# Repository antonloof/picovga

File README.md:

# picovga
VGA output for a Raspberry pi PICO

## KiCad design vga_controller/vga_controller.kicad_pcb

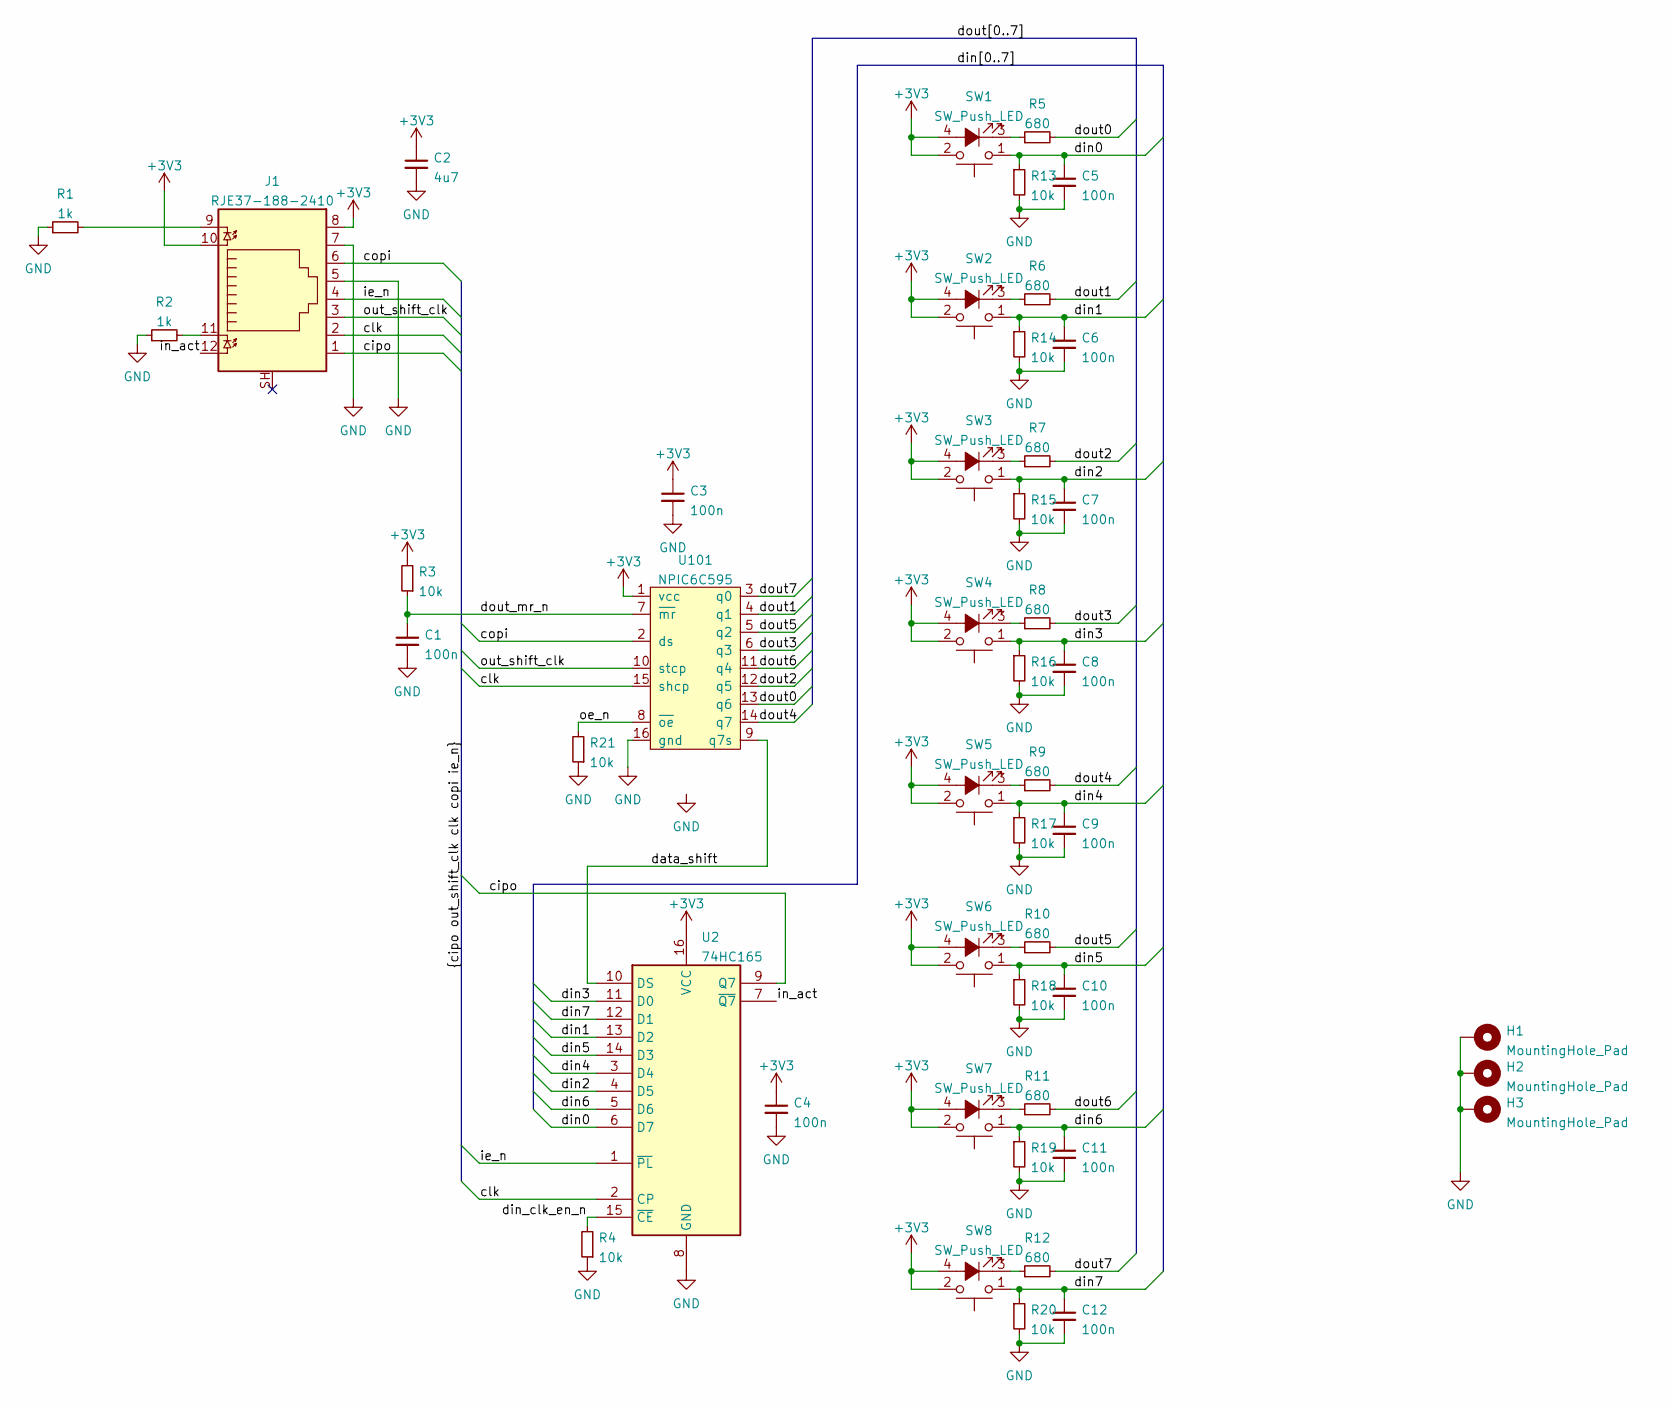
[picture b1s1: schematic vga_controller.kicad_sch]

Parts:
C1, C3, C4, C5, C6, C7, C8, C9, C10, C11, C12: 100n; C_0603_1608Metric_Pad1.08x0.95mm_HandSolder
C2: 4u7; C_0603_1608Metric_Pad1.08x0.95mm_HandSolder
H1, H2, H3: MountingHole_Pad; MountingHole_3.2mm_M3_Pad
J1: RJE37-188-2410; RJ45_Amphenol_RJHSE538X
R1, R2: 1k; R_0603_1608Metric_Pad0.98x0.95mm_HandSolder
R3, R4, R13, R14, R15, R16, R17, R18, R19, R20, R21: 10k; R_0603_1608Metric_Pad0.98x0.95mm_HandSolder
R5, R6, R7, R8, R9, R10, R11, R12: 680; R_0603_1608Metric_Pad0.98x0.95mm_HandSolder
SW1, SW2, SW3, SW4, SW5, SW6, SW7, SW8: SW_Push_LED; SW_Cherry_MX_1.00u_PCB_smd_led
U2: 74HC165; SOIC-16_3.9x9.9mm_P1.27mm
U101: NPIC6C595; SOIC-16_3.9x9.9mm_P1.27mm

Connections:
+3V3: C2.1, C3.1, C4.1, J1.8, J1.10, R3.2, SW1.2, SW1.4 (A), SW2.2, SW2.4 (A), SW3.2, SW3.4 (A), SW4.2, SW4.4 (A), SW5.2, SW5.4 (A), SW6.2, SW6.4 (A), SW7.2, SW7.4 (A), SW8.2, SW8.4 (A), U2.16 (VCC), U101.1 (vcc)
/cipo: J1.1, U2.9 (Q7)
/clk: J1.2, U2.2 (CP), U101.15 (shcp)
/copi: J1.6, U101.2 (ds)
/data_shift: U2.10 (DS), U101.9 (q7s)
/din0: C5.1, R13.1, SW1.1, U2.6 (D7)
/din1: C6.1, R14.1, SW2.1, U2.13 (D2)
/din2: C7.1, R15.1, SW3.1, U2.4 (D5)
/din3: C8.1, R16.1, SW4.1, U2.11 (D0)
/din4: C9.1, R17.1, SW5.1, U2.3 (D4)
/din5: C10.1, R18.1, SW6.1, U2.14 (D3)
/din6: C11.1, R19.1, SW7.1, U2.5 (D6)
/din7: C12.1, R20.1, SW8.1, U2.12 (D1)
/din_clk_en_n: R4.2, U2.15 (~CE)
/dout0: R5.2, U101.13 (q6)
/dout1: R6.2, U101.4 (q1)
/dout2: R7.2, U101.12 (q5)
/dout3: R8.2, U101.6 (q3)
/dout4: R9.2, U101.14 (q7)
/dout5: R10.2, U101.5 (q2)
/dout6: R11.2, U101.11 (q4)
/dout7: R12.2, U101.3 (q0)
/dout_mr_n: C1.1, R3.1, U101.7 (~mr)
/ie_n: J1.4, U2.1 (~PL)
/in_act: J1.12, U2.7 (~Q7)
/oe_n: R21.2, U101.8 (~oe)
/out_shift_clk: J1.3, U101.10 (stcp)
GND: C1.2, C2.2, C3.2, C4.2, C5.2, C6.2, C7.2, C8.2, C9.2, C10.2, C11.2, C12.2, H1.1, H2.1, H3.1, J1.5, J1.7, R1.1, R2.1, R4.1, R13.2, R14.2, R15.2, R16.2, R17.2, R18.2, R19.2, R20.2, R21.1, U2.8 (GND), U101.16 (gnd)
unnamed: J1.9, R1.2
unnamed: J1.11, R2.2
unnamed: R5.1, SW1.3 (K)
unnamed: R6.1, SW2.3 (K)
unnamed: R7.1, SW3.3 (K)
unnamed: R8.1, SW4.3 (K)
unnamed: R9.1, SW5.3 (K)
unnamed: R10.1, SW6.3 (K)
unnamed: R11.1, SW7.3 (K)
unnamed: R12.1, SW8.3 (K)

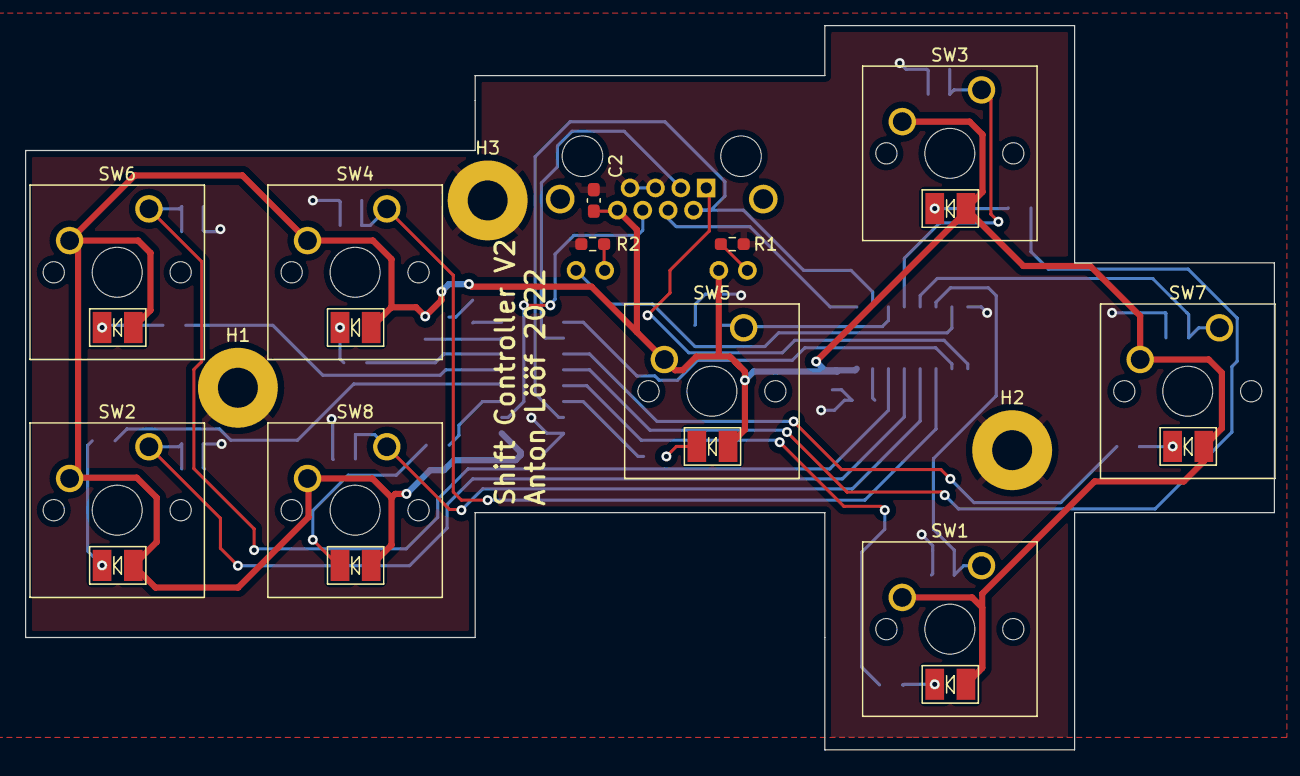
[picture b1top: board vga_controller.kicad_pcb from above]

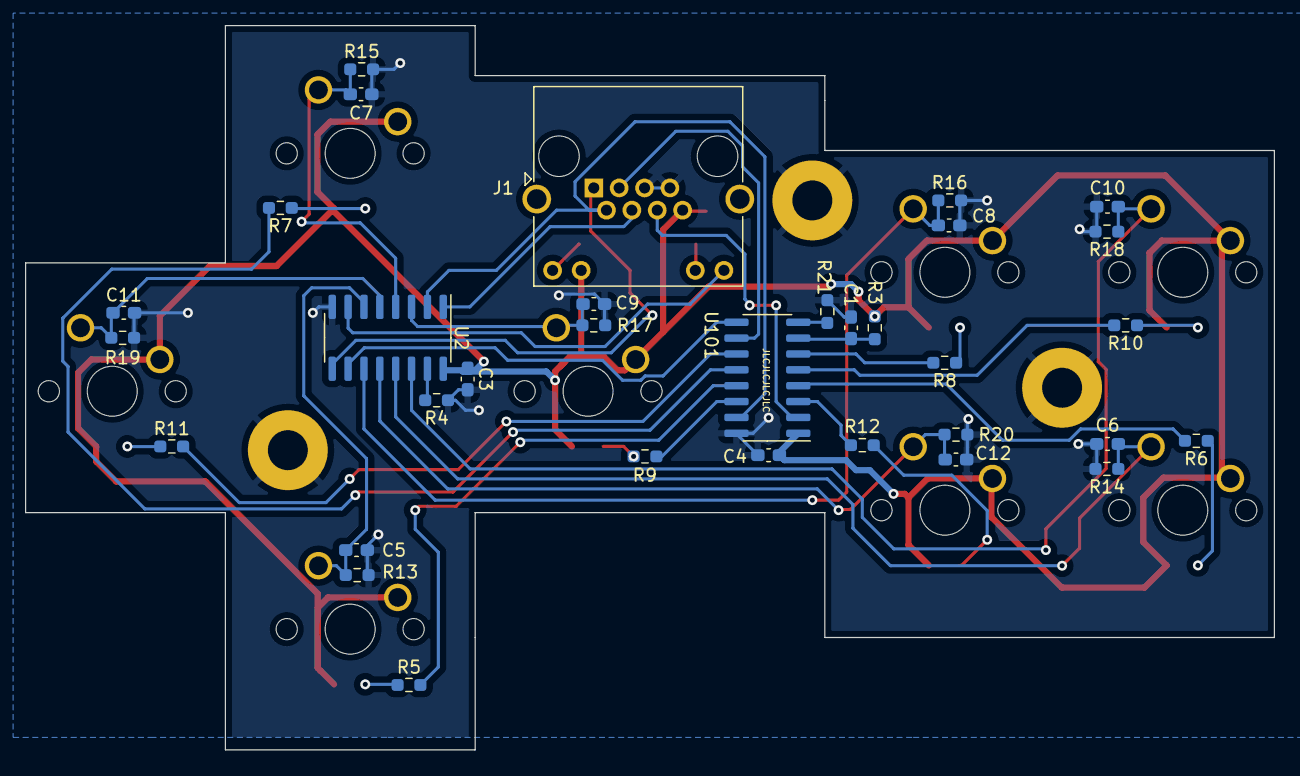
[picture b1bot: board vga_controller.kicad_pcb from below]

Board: 2 copper layers, 100.0 x 58.0 mm, 47 parts (33 on the bottom side), 38 nets.

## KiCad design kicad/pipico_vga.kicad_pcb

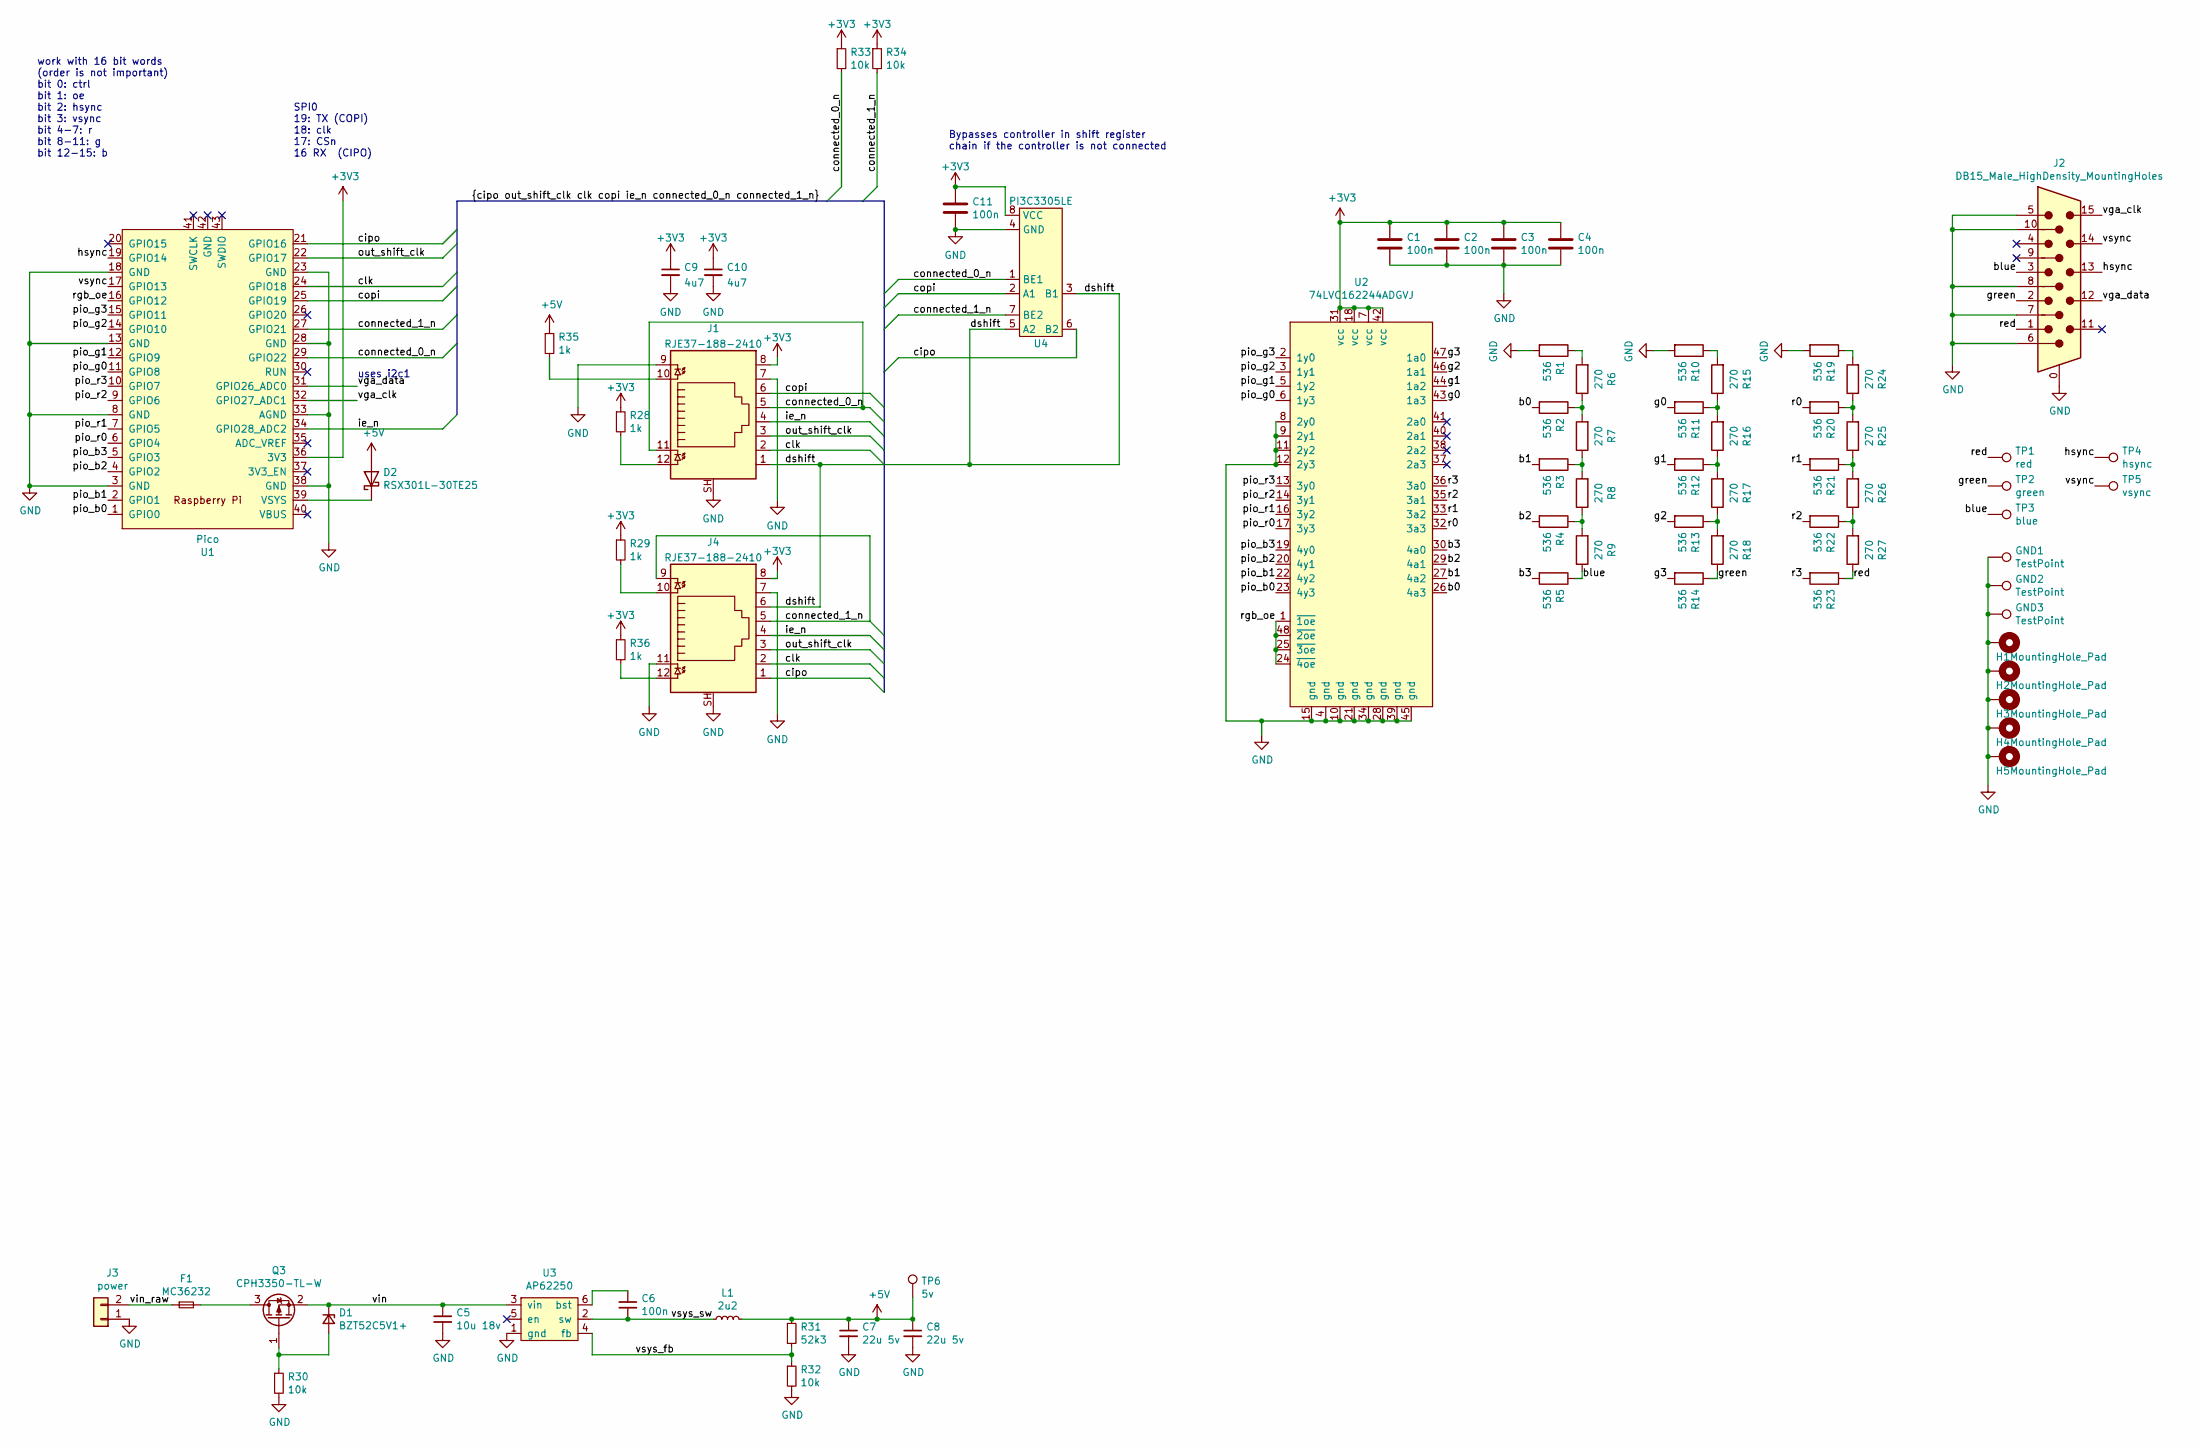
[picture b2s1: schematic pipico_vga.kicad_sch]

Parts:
C1, C2, C3, C4, C6, C11: 100n; C_0603_1608Metric_Pad1.08x0.95mm_HandSolder
C5: 10u 18v; C_1206_3216Metric
C7, C8: 22u 5v; C_0603_1608Metric_Pad1.08x0.95mm_HandSolder
C9, C10: 4u7; C_0603_1608Metric_Pad1.08x0.95mm_HandSolder
D1: BZT52C5V1+; D_SOD-123
D2: RSX301L-30TE25; SOD-106
F1: MC36232; Fuse_1812_4532Metric
GND1, GND2, GND3: TestPoint; TestPoint_THTPad_D2.0mm_Drill1.0mm
H1, H2, H3, H4, H5: MountingHole_Pad; MountingHole_3.2mm_M3_DIN965_Pad
J1, J4: RJE37-188-2410; RJ45_Amphenol_RJHSE538X
J2: DB15_Male_HighDensity_MountingHoles; DSUB-15-HDEX15SNT
J3: power; TerminalBlock_Phoenix_MKDS-1,5-2_1x02_P5.00mm_Horizontal
L1: 2u2; smd_inductor_0806_2016metric
Q3: CPH3350-TL-W; SOT-23_Handsoldering
R1, R2, R3, R4, R5, R10, R11, R12, R13, R14, R19, R20, R21, R22, R23: 536; R_0603_1608Metric_Pad0.98x0.95mm_HandSolder
R6, R7, R8, R9, R15, R16, R17, R18, R24, R25, R26, R27: 270; R_0603_1608Metric_Pad0.98x0.95mm_HandSolder
R28, R29, R35, R36: 1k; R_0603_1608Metric_Pad0.98x0.95mm_HandSolder
R30, R32, R33, R34: 10k; R_0603_1608Metric_Pad0.98x0.95mm_HandSolder
R31: 52k3; R_0603_1608Metric_Pad0.98x0.95mm_HandSolder
TP1: red; TestPoint_THTPad_D2.0mm_Drill1.0mm
TP2: green; TestPoint_THTPad_D2.0mm_Drill1.0mm
TP3: blue; TestPoint_THTPad_D2.0mm_Drill1.0mm
TP4: hsync; TestPoint_THTPad_D2.0mm_Drill1.0mm
TP5: vsync; TestPoint_THTPad_D2.0mm_Drill1.0mm
TP6: 5v; TestPoint_Pad_D2.0mm
U1: Pico; RPi_Pico_SMD_TH
U2: 74LVC162244ADGVJ; SOIC-48
U3: AP62250; TSOT-23-6
U4: PI3C3305LE; TSSOP-8_4.4x3mm_P0.65mm

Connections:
+3V3: C1.1, C2.1, C3.1, C4.1, C9.1, C10.1, C11.1, J1.8, J4.8, R28.1, R29.1, R33.1, R34.1, R36.1, U1.36 (3V3), U2.7 (vcc), U2.18 (vcc), U2.31 (vcc), U2.42 (vcc), U4.8 (VCC)
+5V: C7.1, C8.1, D2.2 (A), L1.2, R31.1, R35.1, TP6.1
/b0: R2.2, U2.26 (4a3)
/b1: R3.2, U2.27 (4a2)
/b2: R4.2, U2.29 (4a1)
/b3: R5.2, U2.30 (4a0)
/blue: J2.3, R5.1, R9.1, TP3.1
/cipo: J4.1, U1.21 (GPIO16), U4.6 (B2)
/clk: J1.2, J4.2, U1.24 (GPIO18)
/connected_0_n: J1.5, J1.11, R33.2, U1.29 (GPIO22), U4.1 (BE1)
/connected_1_n: J4.5, J4.9, R34.2, U1.27 (GPIO21), U4.7 (BE2)
/copi: J1.6, U1.25 (GPIO19), U4.2 (A1)
/dshift: J1.1, J4.6, U4.3 (B1), U4.5 (A2)
/g0: R11.2, U2.43 (1a3)
/g1: R12.2, U2.44 (1a2)
/g2: R13.2, U2.46 (1a1)
/g3: R14.2, U2.47 (1a0)
/green: J2.2, R14.1, R18.1, TP2.1
/hsync: J2.13, TP4.1, U1.19 (GPIO14)
/ie_n: J1.4, J4.4, U1.34 (GPIO28_ADC2)
/out_shift_clk: J1.3, J4.3, U1.22 (GPIO17)
/pio_b0: U1.1 (GPIO0), U2.23 (4y3)
/pio_b1: U1.2 (GPIO1), U2.22 (4y2)
/pio_b2: U1.4 (GPIO2), U2.20 (4y1)
/pio_b3: U1.5 (GPIO3), U2.19 (4y0)
/pio_g0: U1.11 (GPIO8), U2.6 (1y3)
/pio_g1: U1.12 (GPIO9), U2.5 (1y2)
/pio_g2: U1.14 (GPIO10), U2.3 (1y1)
/pio_g3: U1.15 (GPIO11), U2.2 (1y0)
/pio_r0: U1.6 (GPIO4), U2.17 (3y3)
/pio_r1: U1.7 (GPIO5), U2.16 (3y2)
/pio_r2: U1.9 (GPIO6), U2.14 (3y1)
/pio_r3: U1.10 (GPIO7), U2.13 (3y0)
/r0: R20.2, U2.32 (3a3)
/r1: R21.2, U2.33 (3a2)
/r2: R22.2, U2.35 (3a1)
/r3: R23.2, U2.36 (3a0)
/red: J2.1, R23.1, R27.1, TP1.1
/rgb_oe: U1.16 (GPIO12), U2.1 (~1oe), U2.24 (~4oe), U2.25 (~3oe), U2.48 (~2oe)
/vga_clk: J2.15, U1.32 (GPIO27_ADC1)
/vga_data: J2.12, U1.31 (GPIO26_ADC0)
/vin: C5.1, D1.1 (K), Q3.2 (S), U3.3 (vin)
/vin_raw: F1.1, J3.2
/vsync: J2.14, TP5.1, U1.17 (GPIO13)
/vsys_fb: R31.2, R32.1, U3.4 (fb)
/vsys_sw: C6.2, L1.1, U3.2 (sw)
GND: C1.2, C2.2, C3.2, C4.2, C5.2, C7.2, C8.2, C9.2, C10.2, C11.2, GND1.1, GND2.1, GND3.1, H1.1, H2.1, H3.1, H4.1, H5.1, J1.7, J1.9, J1.SH, J2.0, J2.5, J2.6, J2.7, J2.8, J2.10, J3.1, J4.7, J4.11, J4.SH, R1.2, R10.2, R19.2, R30.2, R32.2, U1.3 (GND), U1.8 (GND), U1.13 (GND), U1.18 (GND), U1.23 (GND), U1.28 (GND), U1.33 (AGND), U1.38 (GND), U2.4 (gnd), U2.8 (2y0), U2.9 (2y1), U2.10 (gnd), U2.11 (2y2), U2.12 (2y3), U2.15 (gnd), U2.21 (gnd), U2.28 (gnd), U2.34 (gnd), U2.39 (gnd), U2.45 (gnd), U3.1 (gnd), U4.4 (GND)
unnamed: C6.1, U3.6 (bst)
unnamed: D1.2 (A), Q3.1 (G), R30.1
unnamed: D2.1 (K), U1.39 (VSYS)
unnamed: F1.2, Q3.3 (D)
unnamed: J1.10, R35.2
unnamed: J1.12, R28.2
unnamed: J4.10, R29.2
unnamed: J4.12, R36.2
unnamed: R1.1, R6.2
unnamed: R2.1, R6.1, R7.2
unnamed: R3.1, R7.1, R8.2
unnamed: R4.1, R8.1, R9.2
unnamed: R10.1, R15.2
unnamed: R11.1, R15.1, R16.2
unnamed: R12.1, R16.1, R17.2
unnamed: R13.1, R17.1, R18.2
unnamed: R19.1, R24.2
unnamed: R20.1, R24.1, R25.2
unnamed: R21.1, R25.1, R26.2
unnamed: R22.1, R26.1, R27.2

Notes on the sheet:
work with 16 bit words (order is not important) bit 0: ctrl bit 1: oe bit 2: hsync bit 3: vsync bit 4-7: r bit 8-11: g bit 12-15: b
uses i2c1
SPI0 19: TX (COPI) 18: clk 17: CSn 16 RX (CIPO)
Bypasses controller in shift register chain if the controller is not connected

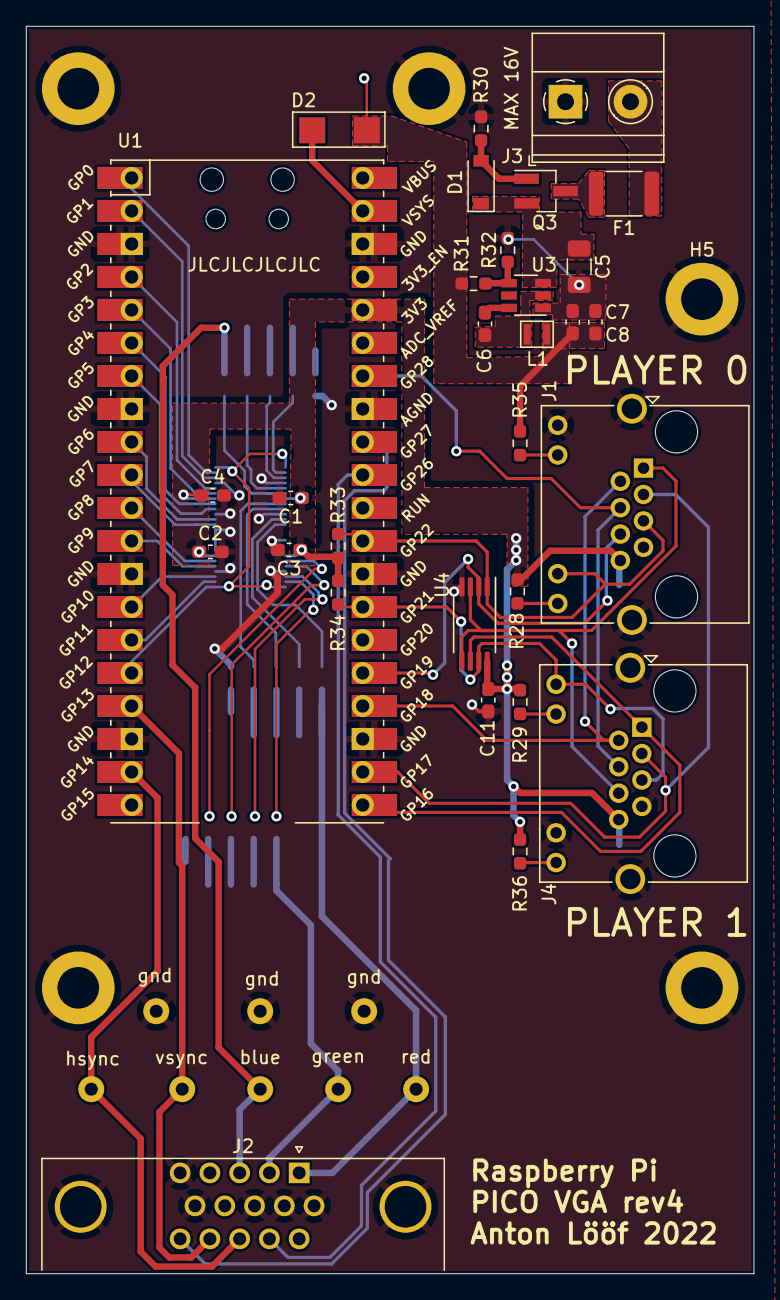
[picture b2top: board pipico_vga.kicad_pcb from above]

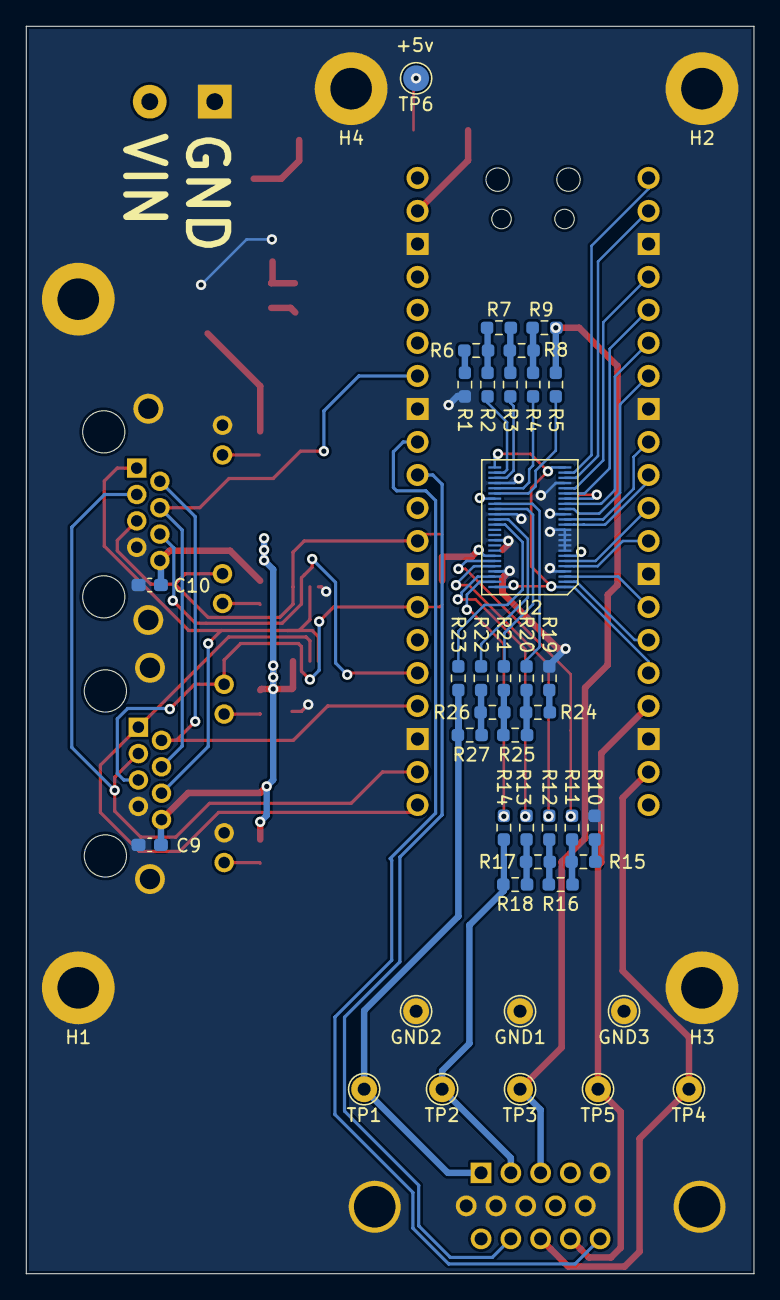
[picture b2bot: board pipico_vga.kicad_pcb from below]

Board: 2 copper layers, 56.0 x 96.0 mm, 74 parts (43 on the bottom side), 67 nets.

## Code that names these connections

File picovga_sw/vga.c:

#include "vga.h"

void vga_dma_irq_handler(void);

void vga_init(vga_pixel *buf1, vga_pixel *buf2, vga_meta *meta)
{
    // init pll
    pll_init(pll_sys, 1, meta->pll_vcof, meta->pll_pd1, meta->pll_pd2);

    // fill up buffers
    meta->row_size = meta->h + meta->row_sync + meta->row_front + meta->row_back;
    // use 2 items for each delay per line
    meta->line_size = meta->w + 2 * meta->line_back + 2 * meta->line_front + 2 * meta->line_sync;
    uint screen_buf_size = meta->row_size * meta->line_size;
    for (uint y = 0; y < meta->h; y++)
    {
        for (uint x = 0; x < meta->w; x++)
        {
            buf1[x + y * meta->line_size].pixel.r = 0;
            buf1[x + y * meta->line_size].pixel.g = 0;
            buf1[x + y * meta->line_size].pixel.b = 0;
            buf1[x + y * meta->line_size].pixel.ctrl = 0;
            buf1[x + y * meta->line_size].pixel.rgb_oe = 0;
            buf1[x + y * meta->line_size].pixel.hsync = 1;
            buf1[x + y * meta->line_size].pixel.vsync = 1;
        }
    }

    memcpy(buf2, buf1, screen_buf_size);

    // init pio
    uint pin_base = 0;
    uint pin_count = 15;
    PIO pio = pio0;
    uint offset = pio_add_program(pio, &vga_program);
    uint sm = pio_claim_unused_sm(pio, true);
    pio_sm_config pio_c = vga_program_get_default_config(offset);
    sm_config_set_out_pins(&pio_c, pin_base, pin_count);
    sm_config_set_fifo_join(&pio_c, PIO_FIFO_JOIN_TX); // could be wrong
    sm_config_set_clkdiv(&pio_c, meta->pio_div);
    sm_config_set_out_shift(&pio_c, false, true, 32);
    for (uint i = pin_base; i < pin_base + pin_count; i++)
    {
        pio_gpio_init(pio, i);
    }
    pio_sm_set_consecutive_pindirs(pio, sm, pin_base, pin_count, true);

    // init dma
    uint dma_c = dma_claim_unused_channel(true);
    dma_channel_config dma_conf = dma_channel_get_default_config(dma_c);
    channel_config_set_read_increment(&dma_conf, true);
    channel_config_set_write_increment(&dma_conf, false);
    channel_config_set_transfer_data_size(&dma_conf, DMA_SIZE_32);
    channel_config_set_dreq(&dma_conf, DREQ_PIO0_TX0 + sm);
    dma_channel_set_irq0_enabled(dma_c, true);
    irq_set_enabled(DMA_IRQ_0, true);
    irq_set_exclusive_handler(DMA_IRQ_0, vga_dma_irq_handler);
    dma_channel_configure(dma_c, &dma_conf, &pio0_hw->txf[sm], NULL, screen_buf_size, false);

    // initialize and enable pio sm
    pio_sm_init(pio, sm, offset, &pio_c);
    pio_sm_set_enabled(pio, sm, true);
}

void vga_dma_irq_handler(void)
{
}

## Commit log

2021-02-19 version 2 of hardware
2021-02-20 Testing some c code
2021-03-02 progress on pcb rev2
2021-03-17 Add v2 PCB
2021-03-17 Add mounting hole
2021-04-21 Rev3 pcb now correct footprint of buffer
2021-08-30 Rev3 pcb and initial SW
2021-08-30 minor
2022-01-11 Start make controller
2022-01-16 schema done, pcb routed
    for controller
2022-01-16 Rev 4 of main board
    controller rev1 done as well :D
2022-01-21 rev4 main and rev1 controller ready for order
2022-04-07 fix issue with controller board
2022-04-07 add more ways to vga
2022-04-07 sw rev3 electricer boogalooer
2022-04-10 some code änna
2022-04-28 vga is ID'd by a screen
2022-05-04 Half working sw
